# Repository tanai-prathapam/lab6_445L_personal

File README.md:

# Lab 6 Introduction to PCB Design

## Table of Contents

- [Lab 6 Introduction to PCB Design](#lab-6-introduction-to-pcb-design)
---

## 0 Repository Structure

The typical explanation for the repo structure. Lab specific instructions can be
found further below.

### 0.1 HW

The `hw` folder should contain your schematic and board files for your PCB or
circuits. In labs 1-5 and 10, you will be creating schematics for your circuit
in EAGLE. A setup tutorial can be found
[here](https://www.shawnvictor.net/autodesk-eagle.html).

### 0.2 SW

The `sw` folder should contain your application firmware and software written
for the lab. The `sw/inc` folder contains firmware drivers written for you by
Professor Valvano. Feel free to write your own (in fact, in some labs, you may
be required to write your own).

You can place any other source files in the `sw` folder. TAs will look at the
files you create and/or modify for software quality and for running your
project.

### 0.3 Resources

A couple files are provided in the Resources folder so you don't have to keep
searching for that one TI document. Some of them are immediately useful, like
the TM4C datasheet. Others may be useful for your final project, like the
TM4C_System_Design_Guidelines page.

### 0.4 Git and Github

We will extensively use Git and Github for managing lab projects. This makes it
easier for TAs to grade and help debug the project by allowing us to see commit
histories, maintain a common project structure, and likewise, it makes it easier
for students to collaborate with partners, merge different codebases, and to
debug their work by having a history of commits.

Two common ways of using Git and Github are [Github Desktop](https://desktop.github.com/) and the [command line](https://git-scm.com/downloads).
[Tutorials](https://dev.to/mollynem/git-github--workflow-fundamentals-5496) are also abundant on the net for you to peruse. We've provided a cheatsheet for git
in the Resources folder.

It is highly recommended to make the most out of Git, even if you've never used
it before. Version control will save you a lot of suffering, and tools like Git
or SVN are ubiquitous in the industry.

A gitignore file is added to the root of this repo that may prevent specific
files from being tagged to the repo. This are typically autogenerated output
files we don't care about, but sometimes other stuff (like .lib files) falls
through that we want. Feel free to modify if necessary.

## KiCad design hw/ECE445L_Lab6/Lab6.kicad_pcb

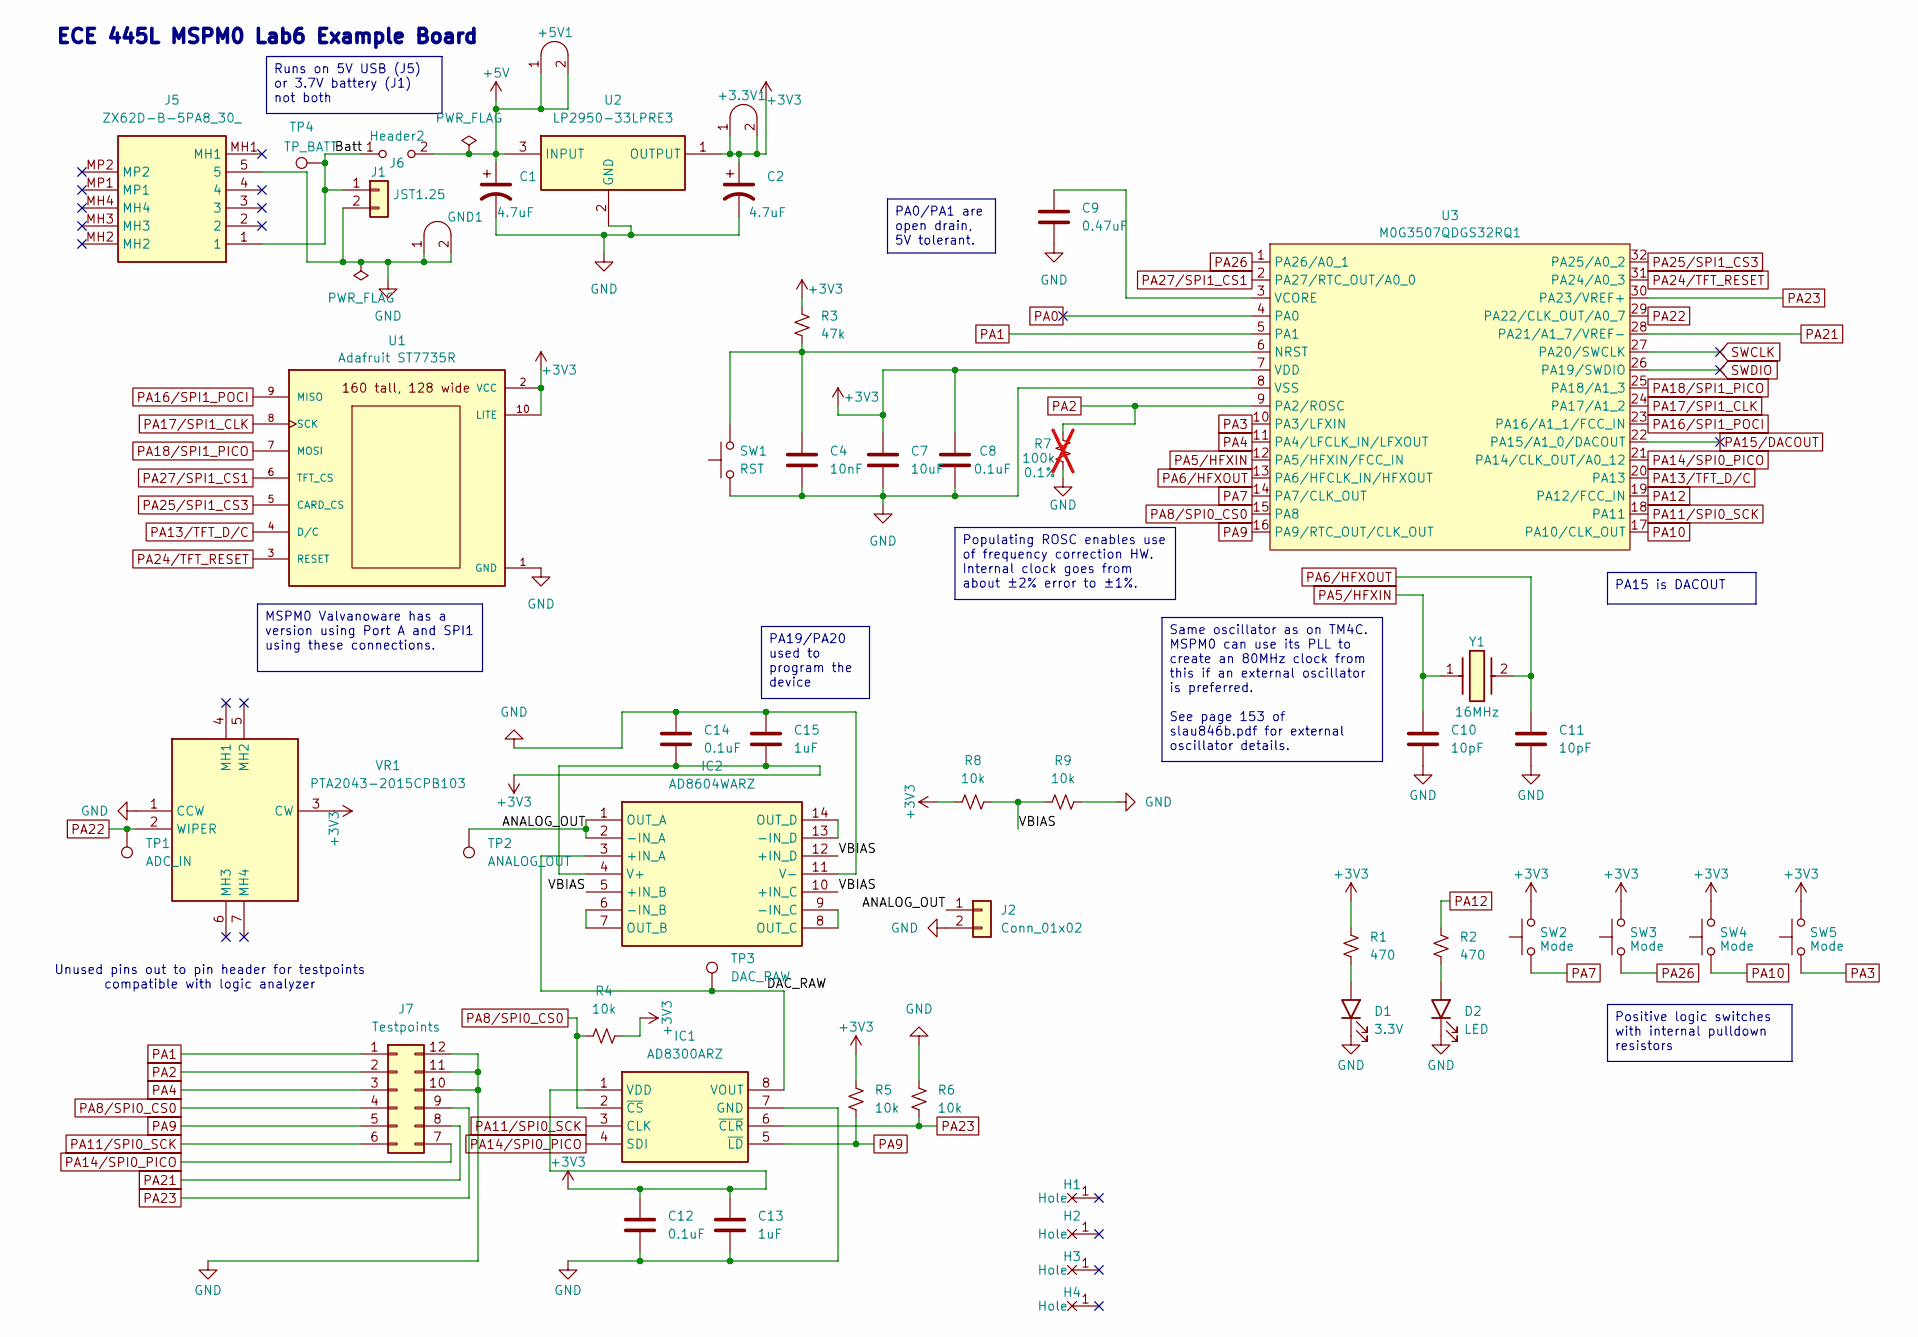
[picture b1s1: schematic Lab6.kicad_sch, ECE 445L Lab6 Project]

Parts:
+3.3V1: +3.3V; Testpoint_1x02_P2.54mm
+5V1: +5V; Testpoint_1x02_P2.54mm
C1, C2: 4.7uF; CP_Radial_Tantal200mil
C4: 10nF; C_Radial_100mil
C7: 10uF; C_Rect_L4.6mm_W3.8mm_P2.50mm_MKS02_FKP02
C8, C12, C14: 0.1uF; C_Rect_L4.6mm_W3.8mm_P2.50mm_MKS02_FKP02
C9: 0.47uF; C_Rect_L7.0mm_W3.5mm_P2.50mm_P5.00mm
C10, C11: 10pF; C_Rect_L4.0mm_W2.5mm_P2.50mm
C13, C15: 1uF; C_Rect_L4.0mm_W2.5mm_P2.50mm
D1: 3.3V; LED_D5.0mm
D2: LED; LED_D5.0mm
GND1: GND; Testpoint_1x02_P2.54mm
H1, H2, H3, H4: MountingHole_4_40
IC1: AD8300ARZ; SOIC127P600X175-8N; Manufacturer_Part_Number AD8300ARZ; Mouser Part Number 584-AD8300ARZ
IC2: AD8604WARZ; SOIC-14_3.9x8.7mm_P1.27mm; Manufacturer_Part_Number AD8604WARZ; Mouser Part Number 584-AD8604WARZ
J1: JST1.25; Molex_PicoBlade_53047-0210_1x02_P1.25mm_Vertical
J2: Conn_01x02; PinHeader_1x02_P2.54mm_Vertical
J5: ZX62D-B-5PA8_30_; ZX62DB5PA830; Mouser Part Number 798-ZX62D-B-5PA830
J6: Header2; PinHeader_1x02_P2.54mm_Vertical
J7: Testpoints; PinHeader_2x06_P2.54mm_Vertical
R1, R2: 470; R_Axial_DIN0204_L3.6mm_D1.6mm_P7.62mm_Horizontal
R3: 47k; R_Axial_DIN0204_L3.6mm_D1.6mm_P7.62mm_Horizontal
R4, R5, R6, R8, R9: 10k; R_Axial_DIN0204_L3.6mm_D1.6mm_P7.62mm_Horizontal
R7: 100k; R_Axial_DIN0204_L3.6mm_D1.6mm_P7.62mm_Horizontal; Tolerance 0.1%; not fitted
SW1: RST; SW_PUSH_6mm
SW2, SW3, SW4, SW5: Mode; SW_PUSH_6mm
TP1: ADC_IN; TestPoint_Pad_D2.0mm
TP2: ANALOG_OUT; TestPoint_Pad_D2.0mm
TP3: DAC_RAW; TestPoint_Pad_D2.0mm
TP4: TP_BATT; TestPoint_THTPad_D2.0mm_Drill1.0mm
U1: Adafruit ST7735R; adafruit_st7735r2
U2: LP2950-33LPRE3; TL431CLPM; Mouser Part Number 595-LP2950-33LPRE3
U3: M0G3507QDGS32RQ1; generic_VSSOP_0.5mm
VR1: PTA2043-2015CPB103; PTA20432015CPB103; Manufacturer_Part_Number PTA2043-2015CPB103; Mouser Part Number 652-PTA20432015CPB10
Y1: 16MHz; ABM3; Mouser Part Number 815-ABM3-16-B2-T

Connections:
+3V3: +3.3V1.1 (A), +3.3V1.2 (B), C2.1, C7.1, C8.1, C12.1, C13.1, C14.2, C15.2, IC1.1 (VDD), IC2.4 (V+), R1.2, R3.1, R4.1, R5.1, R8.1, SW2.2, SW3.2, SW4.2, SW5.2, U1.2 (VCC), U1.10 (LITE), U2.1 (OUTPUT), U3.7 (VDD), VR1.3 (CW); also elsewhere on the board
+5V: +5V1.1 (A), +5V1.2 (B), C1.1, J6.2 (B), U2.3 (INPUT)
/ANALOG_OUT: IC2.1 (OUT_A), IC2.2 (-IN_A), J2.1, TP2.1 (1_1)
/Batt: J1.1, J5.1, J6.1 (A), TP4.1 (1_1)
/DAC_RAW: IC1.8 (VOUT), IC2.3 (+IN_A), TP3.1 (1_1)
/VBIAS: IC2.5 (+IN_B), IC2.10 (+IN_C), IC2.12 (+IN_D), R8.2, R9.1
unnamed: D1.2 (A), R1.1
unnamed: D2.2 (A), R2.1
unnamed: IC2.6 (-IN_B), IC2.7 (OUT_B)
unnamed: IC2.8 (OUT_C), IC2.9 (-IN_C)
unnamed: IC2.13 (-IN_D), IC2.14 (OUT_D)
unnamed: C4.1, R3.2, SW1.2, U3.6 (NRST)
PA0: U3.4 (PA0)
PA1: J7.1, U3.5 (PA1)
PA2: J7.2, R7.2, U3.9 (PA2/ROSC)
PA3: SW5.1, U3.10 (PA3/LFXIN)
PA4: J7.3, U3.11 (PA4/LFCLK_IN/LFXOUT)
PA5/HFXIN: C10.1, U3.12 (PA5/HFXIN/FCC_IN), Y1.1
PA6/HFXOUT: C11.1, U3.13 (PA6/HFCLK_IN/HFXOUT), Y1.2
PA7: SW2.1, U3.14 (PA7/CLK_OUT)
PA8/SPI0_CS0: IC1.2 (~CS), J7.4, R4.2, U3.15 (PA8)
PA9: IC1.5 (~LD), J7.5, R5.2, U3.16 (PA9/RTC_OUT/CLK_OUT)
PA10: SW4.1, U3.17 (PA10/CLK_OUT)
PA11/SPI0_SCK: IC1.3 (CLK), J7.6, U3.18 (PA11)
PA12: R2.2, U3.19 (PA12/FCC_IN)
PA13/TFT_D/C: U1.4 (D/C), U3.20 (PA13)
PA14/SPI0_PICO: IC1.4 (SDI), J7.7, U3.21 (PA14/CLK_OUT/A0_12)
PA15/DACOUT: U3.22 (PA15/A1_0/DACOUT)
PA16/SPI1_POCI: U1.9 (MISO), U3.23 (PA16/A1_1/FCC_IN)
PA17/SPI1_CLK: U1.8 (SCK), U3.24 (PA17/A1_2)
PA18/SPI1_PICO: U1.7 (MOSI), U3.25 (PA18/A1_3)
PA21: J7.8, U3.28 (PA21/A1_7/VREF-)
PA22: TP1.1 (1_1), U3.29 (PA22/CLK_OUT/A0_7), VR1.2 (WIPER)
PA23: IC1.6 (~CLR), J7.9, R6.2, U3.30 (PA23/VREF+)
PA24/TFT_RESET: U1.3 (RESET), U3.31 (PA24/A0_3)
PA25/SPI1_CS3: U1.5 (CARD_CS), U3.32 (PA25/A0_2)
PA26: SW3.1, U3.1 (PA26/A0_1)
PA27/SPI1_CS1: U1.6 (TFT_CS), U3.2 (PA27/RTC_OUT/A0_0)
SWCLK: U3.27 (PA20/SWCLK); also elsewhere on the board
SWDIO: U3.26 (PA19/SWDIO); also elsewhere on the board

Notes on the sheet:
Unused pins out to pin header for testpoints compatible with logic analyzer
ECE 445L MSPM0 Lab6 Example Board
Runs on 5V USB (J5) or 3.7V battery (J1) not both
PA19/PA20 used to program the device
Positive logic switches with internal pulldown resistors
MSPM0 Valvanoware has a version using Port A and SPI1 using these connections.
PA0/PA1 are open drain, 5V tolerant.
PA15 is DACOUT
Same oscillator as on TM4C. MSPM0 can use its PLL to create an 80MHz clock from this if an external oscillator is preferred. See page 153 of slau846b.pdf for external oscillator details.
Populating ROSC enables use of frequency correction HW. Internal clock goes from about ±2% error to ±1%.

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
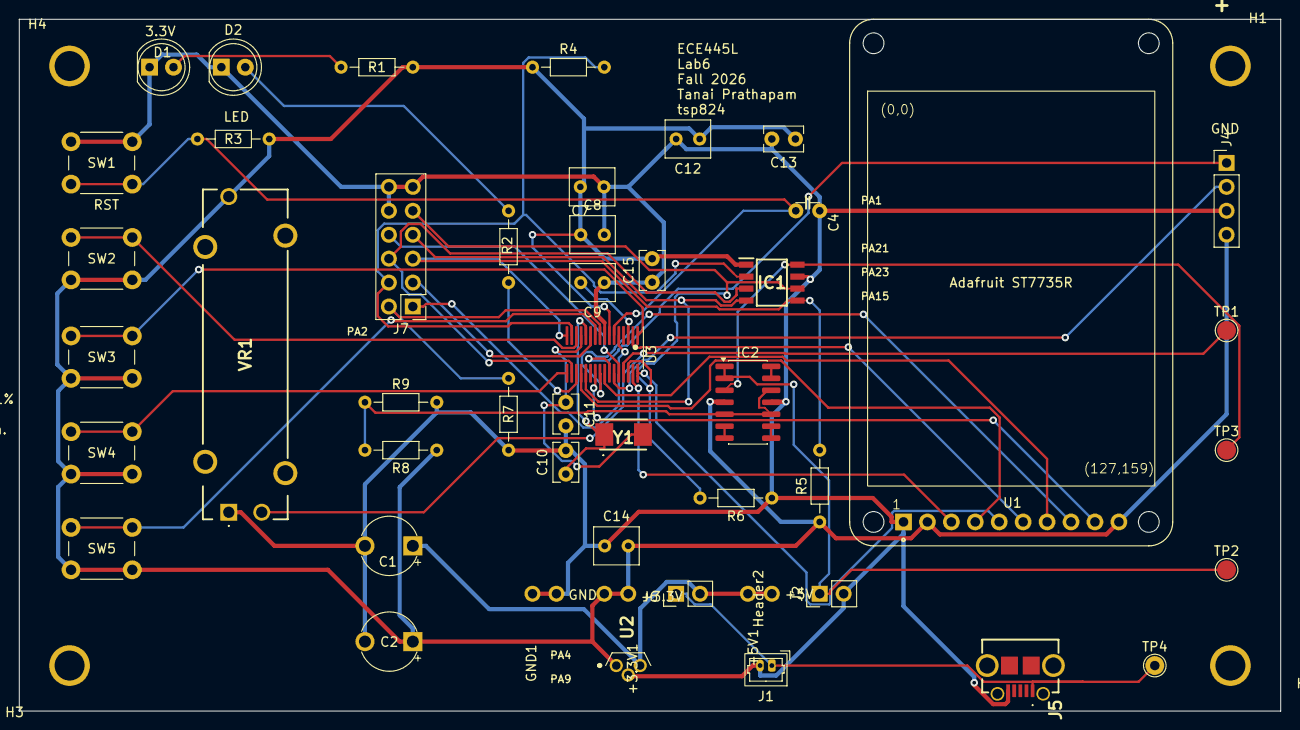
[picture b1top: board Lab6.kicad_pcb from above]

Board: 2 copper layers, 133.9 x 73.4 mm, 52 parts (0 on the bottom side), 40 nets.

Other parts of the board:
J4: Debugger; PinHeader_1x04_P2.54mm_Vertical

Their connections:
+3V3: J4.4 (C); also elsewhere on the board
SWCLK: J4.2 (B); also elsewhere on the board
SWDIO: J4.1 (A); also elsewhere on the board

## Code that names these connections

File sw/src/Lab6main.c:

// Lab6main.c
// Runs on M0G3507QDGS32RQ1
// Mark McDermott, Daniel Valvano and Jonathan Valvano
// Students do not need to use this project. 
// It is here to help with understanding single chip software
// July 4, 2026

// ********NOT A LAUNCHPAD****************
// Specify your hardware connections, feel free to change
// 16 MHz crystal connected across, 10pF C0G capacitors to ground
//   PA5 is HFXIN
//   PA6 is HFXOUT
// PA0  is squarewave output to buzzer
// PA3  is SW5 
// PA10 is SW4 
// PA26 is SW3 
// PA7  is SW2
// PA22 is ADC input from slide pot, ADC0 channel 7
// PA15 is DAC output to speaker
// **********ST7735 TFT and SDC*******************
// ST7735, ECE445L Lab 6, 7 VSSOP-32 M0G3507QDGS32RQ1
// Backlight (pin 10)     to +3.3 V
// MISO (pin 9)           to SPI1 POCI: PA16
// SCK (pin 8)            to SPI1 SCLK: PA17
// MOSI (pin 7)           to SPI1 PICO: PA18
// TFT_CS (pin 6)         to GPIO:  PA27
// CARD_CS (pin 5)        to PA25 (GPIO)
// Data/Command (pin 4)   to PA13 (GPIO), high for data, low for command
// RESET (pin 3)          to PA24 (GPIO)
// VCC (pin 2)            to +3.3 V
// Gnd (pin 1)            to ground

#include <ti/devices/msp/msp.h>
#include <stdio.h>
#include "../inc/LaunchPad.h"
#include "../inc/Clock.h"
#include "../inc/ST7735_SDC.h"
#include "../inc/Timer.h"
#include "../inc/DAC.h"
#include "../inc/ADC.h"

#define BUZ_PORT      GPIOA
#define BUZ_PIN       (1<<0)      // PA0
#define BUZ_INDEX     (PA0INDEX)  // PA0 GPIO

#define LED_PORT      GPIOA
#define LED_PIN       (1<<12)      // PA12
#define LED_INDEX     (PA12INDEX)  // PA12 GPIO
#define LED_Toggle()  LED_PORT->DOUTTGL31_0 = LED_PIN
#define SW5_PORT      GPIOA
#define SW5_PIN       (1<<3)       // PA3
#define SW5_INDEX     (PA3INDEX)   // PA3 GPIO
#define SW4_PORT      GPIOA
#define SW4_PIN       (1<<10)      // PA10
#define SW4_INDEX     (PA10INDEX)  // PA10 GPIO
#define SW3_PORT      GPIOA
#define SW3_PIN       (1<<26)      // PA26
#define SW3_INDEX     (PA26INDEX)  // PA26 GPIO
#define SW2_PORT      GPIOA
#define SW2_PIN       (1<<7)       // PA7
#define SW2_INDEX     (PA7INDEX)   // PA7 GPIO
#define SW(pin) (SW ## pin ##_PORT->DIN31_0&SW ## pin ##_PIN)

// 12-bit 64-element sine wave
const uint16_t Wave[64] = {
  2048,2244,2438,2629,2813,2991,3159,3317,3462,3594,3711,
  3812,3896,3962,4010,4038,4048,4038,4010,3962,3896,3812,
  3711,3594,3462,3317,3159,2991,2813,2629,2438,2244,2048,
  1852,1658,1467,1283,1105,937,779,634,502,385,284,
  200,134,86,58,48,58,86,134,200,284,385,
  502,634,779,937,1105,1283,1467,1658,1852
}; 
uint32_t count2,count3,count4;
void SysTick_Handler(void){
  if(SW(2)){
    DAC_Out(Wave[count2&0x3F]);
    count2++;
  }
}
uint32_t data,distance,time,sum,flag;

void TIMG8_IRQHandler(void){// runs every 1ms
  if((TIMG8->CPU_INT.IIDX) == 1){ // this will acknowledge
    if(SW(3)){
      BUZ_PORT->DOUTTGL31_0 = BUZ_PIN;
      count3++;
    }else{
      BUZ_PORT->DOUTCLR31_0 = BUZ_PIN;
    }
    data = ADC0_In();
    sum += data;
    time++;
    if(time >= 128){
      distance = (2000*sum)>>(7+12); // 0.001cm
      time = 0;
      sum = 0;
      flag = 1; // mailbox flag
    }
  }
}
void LED_Init(void);
void Buzzer_Init(void);
void Switch_Init(void);
void ActivatePortA(void);
void SysTick_InitArm(uint32_t period, uint32_t priority);
int main0(void){ // main0 test of M0G3507QDGS32RQ1 with I/O devices
  __disable_irq(); 
  ActivatePortA();
  Clock_Init_HFXT_16_80MHz(0);  // 0.005% accurate running off external crystal oscillator

  LED_Init();
  Buzzer_Init();
  Switch_Init();
  DAC_Init();
  ADC0_Init(7,ADCVREF_VDDA);
  time = sum = count2 = count3 = count4 = 0;
  TimerG8_IntArm(1000,40,1);   // TimerG0 trigger every 1ms 
  SysTick_InitArm(80000/64,0); // 64kHz

  __enable_irq();
  while(1){
    if(SW(4)){
      LED_Toggle();
      count4++;
    }
    Clock_Delay(40000000); // 500ms
  }
}

// place scope or login analyzer to PA0 or PA10
// each the following five clock options should create 50 Hz squarewave
int main1(void){ // main1 test of clocks and PLL
  __disable_irq(); 
  ActivatePortA(); 
  // default is 32MHz SYSOSC    // 0.7% accurate running off internal oscillator
  // Clock_Init(OSCFREQ4MHZ);   // 0.7% accurate running off internal oscillator
  // Clock_Init(OSCFREQ32MHZ);  // 0.7% accurate running off internal oscillator
  // Clock_Init80MHz(0);        // 0.7% accurate running off internal oscillator
  // Clock_Init_HFXT_16MHz();   // 0.005% accurate running off external crystal oscillator
  Clock_Init_HFXT_16_80MHz(0);  // 0.005% accurate running off external crystal oscillator
  Buzzer_Init();
  LED_Init();
  ADC0_Init(7,ADCVREF_VDDA);
  time = sum = count2 = count3 = count4 = 0;
  TimerG8_IntArm(1000,40,1);   // TimerG0 trigger every 1ms 

  while(1){
    LED_Toggle();
    BUZ_PORT->DOUTTGL31_0 = BUZ_PIN;
    count4++;
    Clock_Delay(Clock_Freq()/100); // 10ms
  } 
} 

int main(void){ // main2 test of LCD
  __disable_irq(); 
  ActivatePortA(); 
  Clock_Init_HFXT_16_80MHz(0);  // 0.005% accurate running off external crystal oscillator
  Buzzer_Init();
  LED_Init();
  TIMG0->COUNTERREGS.CTRCTL &= ~0x01; // disarm if not using SDC
  ST7735_InitR(INITR_REDTAB); //INITR_REDTAB for AdaFruit, INITR_BLACKTAB for SPI HiLetgo ST7735R
  ST7735_FillScreen(ST7735_BLACK);
  ST7735_SetCursor(0, 0);  
  ST7735_OutString("ECE445L Lab 6\n");
  ST7735_OutString("Valvano");
  ST7735_PlotClear(0,2000);  // range from 0 to 2000 0.001cm
  ADC0_Init(7,ADCVREF_VDDA);
  time = sum = count2 = count3 = count4 = flag=0;
 // TimerG8_IntArm(1000,40,1);   // TimerG0 trigger every 1ms 
  BUZ_PORT->DOUTSET31_0 = BUZ_PIN;
  __enable_irq();
  while(1){
    if(flag){
      flag = 0;
      LED_Toggle();
      count4++;
      ST7735_PlotPoint(distance);
      ST7735_PlotNextErase();
    }
  } 
} 




void Buzzer_Init(void){
   // PA0 is squarewave output to buzzer
  IOMUX->SECCFG.PINCM[BUZ_INDEX]  = (uint32_t) 0x00000081;
  BUZ_PORT->DOE31_0 |= BUZ_PIN;
  BUZ_PORT->DOUTCLR31_0 = BUZ_PIN;
}
void Switch_Init(void){
// PA3, PA7, PA10, PA26
  IOMUX->SECCFG.PINCM[SW2_INDEX]  = (uint32_t) 0x00050081; // input, pull down;
  IOMUX->SECCFG.PINCM[SW3_INDEX]  = (uint32_t) 0x00050081; // input, pull down;
  IOMUX->SECCFG.PINCM[SW4_INDEX]  = (uint32_t) 0x00050081; // input, pull down;
  IOMUX->SECCFG.PINCM[SW5_INDEX]  = (uint32_t) 0x00050081; // input, pull down;
}

void ActivatePortA(void){
    // Reset t GPIO peripherals
    // RSTCLR
    //   bits 31-24 unlock key 0xB1
    //   bit 1 is Clear reset sticky bit
    //   bit 0 is reset gpio port
  GPIOA->GPRCM.RSTCTL = (uint32_t)0xB1000003;

    // Enable power to two GPIO peripherals
    // PWREN
    //   bits 31-24 unlock key 0x26
    //   bit 0 is Enable Power
  GPIOA->GPRCM.PWREN = (uint32_t)0x26000001;

  Clock_Delay(24); // time for gpio to power up
}
void LED_Init(void){
  IOMUX->SECCFG.PINCM[LED_INDEX]  = (uint32_t) 0x00000081;
  LED_PORT->DOE31_0 |= LED_PIN;
  LED_PORT->DOUTCLR31_0 = LED_PIN;
}
void LED_Out(uint32_t data){
  if(data){
    LED_PORT->DOUTSET31_0 = LED_PIN; // on
  }else{
    LED_PORT->DOUTCLR31_0 = LED_PIN; // off
  }

}


// ------------------    SysTick_Init     ------------------------------------
// Initialize Systick periodic interrupts
// Input:  interrupt period
//            Units of period are 12.5ns
//            Maximum is 2^24-1
//            Minimum is determined by length of ISR
// Output: none
void SysTick_InitArm(uint32_t period, uint32_t priority){
  SysTick->CTRL  = 0x00;      // disable during initialization
  SysTick->LOAD  = period-1;  // set reload register
  //The ARM Cortex-M0+ only implements the most significant 2 bits of each 8-bit priority field (giving the 4 priority levels).
  SCB->SHP[1]    = (SCB->SHP[1]&(~0xC0000000))|priority<<30;    // set priority (bits 31,30)
  SysTick->VAL   = 0;         // clear count, cause reload
  SysTick->CTRL  = 0x07;      // Enable SysTick IRQ and SysTick Timer
}

// Executed every 1 ms, armed by ST7735_InitR
// this should not trigger because you should disarm G0 timer
// remove this ISR if using the SDC
void TIMG0_IRQHandler(void){
  if((TIMG0->CPU_INT.IIDX) == 1){ // this will acknowledge
// the SDC interface will use this
  }
}
